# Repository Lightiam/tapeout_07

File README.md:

# Tapeout 07

Controlled repository upload for the Tapeout July_04 work performed so far.

## Start Here

For the manufacturer's current request, use only:

- `00_step01_gerber_bom_only/TFLN_AI_NODE_X2_STEP_01_GERBER_REVIEW.zip`
- `00_step01_gerber_bom_only/TFLN_AI_NODE_X2_STEP_01_BOM.xlsx`

Those are the controlled Step 01 Gerber/BOM review files. The Gerber zip has been refreshed from the post-cleanup KiCad export, and the BOM workbook has been updated to remove stale caution wording, old DRC counts, and old mechanical-reference wording.

## Other Folders

- `01_full_template_outputs`: full template-output package and indexes.
- `02_do_over_vlsi_flow`: VLSI/PCB do-over flow package and response docs.
- `03_schematic_transmittal`: schematic transmittal package and clear dual-NCE/TFLN overview.
- `04_rebuild_eco_required`: reference-envelope rebuild package requiring engineering ECO closure.
- `05_manufacturer_messages`: sendable manufacturer messages and clarification questions.
- `06_engineering_notes`: ECO candidate traceability evidence.
- `07_engineering_reconcile`: latest patched KiCad source and KiCad validation delta.
- `08_fab_release`: fabrication-readiness package — placement audit, fab notes, drill/centroid data, decision log, and release gate.
- `09_pin_complete_data`: pin-data resolution matrix, datasheet manifest, and the engineering data request for the missing NCE/HBM4/TFLN pin maps.
- `10_fab_readiness`: current fab-readiness control point and release-gate verdict. **Start here for fab status.**
- `11_production_fab_roadmap`: real-world sourcing decisions (HBM3E substitute, HyperLight TFLN target) and the locked-layout agent prompt for closing the remaining gaps. **Start here for the active work plan.**
- `99_generation_scripts`: scripts used to generate/assemble these artifacts.

## Engineering Status

Current validated status as of 2026-07-07:

- The repo does not contain a complete design-source schematic or external netlist. The checked KiCad schematic is a connectivity stub: 2,311 lines, 28 wire objects, 82 schematic symbols, and 0 explicit net entries.
- Non-netlist manufacturability cleanup has been applied in `07_engineering_reconcile/00_OPEN_IN_KICAD_PATCHED/`: 4-layer High-Tg FR4 review stackup, ENIG finish metadata, six board-only fiducials, project-local footprint libraries, and silkscreen cleanup.
- The Step 01 BOM workbook now carries current review/signoff language and current validation counts instead of the earlier stale status wording.
- `07_engineering_reconcile/after_non_netlist_fab_readiness_drc.json` reports 0 DRC errors, 0 unconnected items, 82 DRC warnings, and 214 schematic-parity warnings.
- The 82 remaining DRC warnings are all `lib_footprint_mismatch`. The 214 schematic-parity warnings require a real schematic/netlist source and cannot be closed by file cleanup alone.

Post-cleanup Gerber/drill engineering-review export:

- `07_engineering_reconcile/TFLN_AI_NODE_X2_AFTER_NON_NETLIST_CLEANUP_GERBER_DRILL.zip`

## Fabrication Readiness

The `08_fab_release/` package from the remote branch remains in the repo as the fabrication-readiness evidence package: placement audit, fab notes, drill/centroid data, decision log, and release gate. Treat it together with `07_engineering_reconcile/`: production approval still depends on complete schematic/netlist source, parity closure or signed waiver, BOM owner signoff, chassis/mechanical signoff, and manufacturer DFM/DFA closure.

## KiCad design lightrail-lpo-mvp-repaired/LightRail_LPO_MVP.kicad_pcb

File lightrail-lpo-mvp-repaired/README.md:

# LightRail LPO MVP — Manufacturing & Production Package

This package contains the complete manufacturing and SMT assembly deliverables for the **LightRail LPO MVP** board.

## Package Contents

1. **BOM.csv** — Bill of Materials with Designators, Manufacturer Part Numbers (MPNs), Values, Footprints, and Quantities.
2. **CPL.csv** — Component Placement List (Centroid / XY file) containing designator coordinates (X/Y mm, rotation, board layer).
3. **Assembly_Top.svg** — Top-side SMT assembly placement drawing.
4. **Assembly_Bottom.svg** — Bottom-side SMT assembly placement drawing.
5. **KiCad Source Files** — Full PCB design source:
   - `LightRail_LPO_MVP.kicad_pro` (KiCad Project file)
   - `LightRail_LPO_MVP.kicad_sch` (KiCad Schematic file)
   - `LightRail_LPO_MVP.kicad_pcb` (KiCad PCB Layout file)

## Gerber Export Instructions

Gerber plot parameters are pre-configured inside the `LightRail_LPO_MVP.kicad_pcb` source file for automatic plotting. To export:
1. Open `LightRail_LPO_MVP.kicad_pcb` in KiCad Layout Editor.
2. Go to **File → Plot...** (or click the Plot icon).
3. Verify the Output Directory is set to `gerbers/`.
4. Click **Plot** to generate Gerber layers (Copper, Mask, Silk, Paste, Edge.Cuts).
5. Click **Generate Drill Files...** and click **Generate Drill File** to export Excellon drill data.

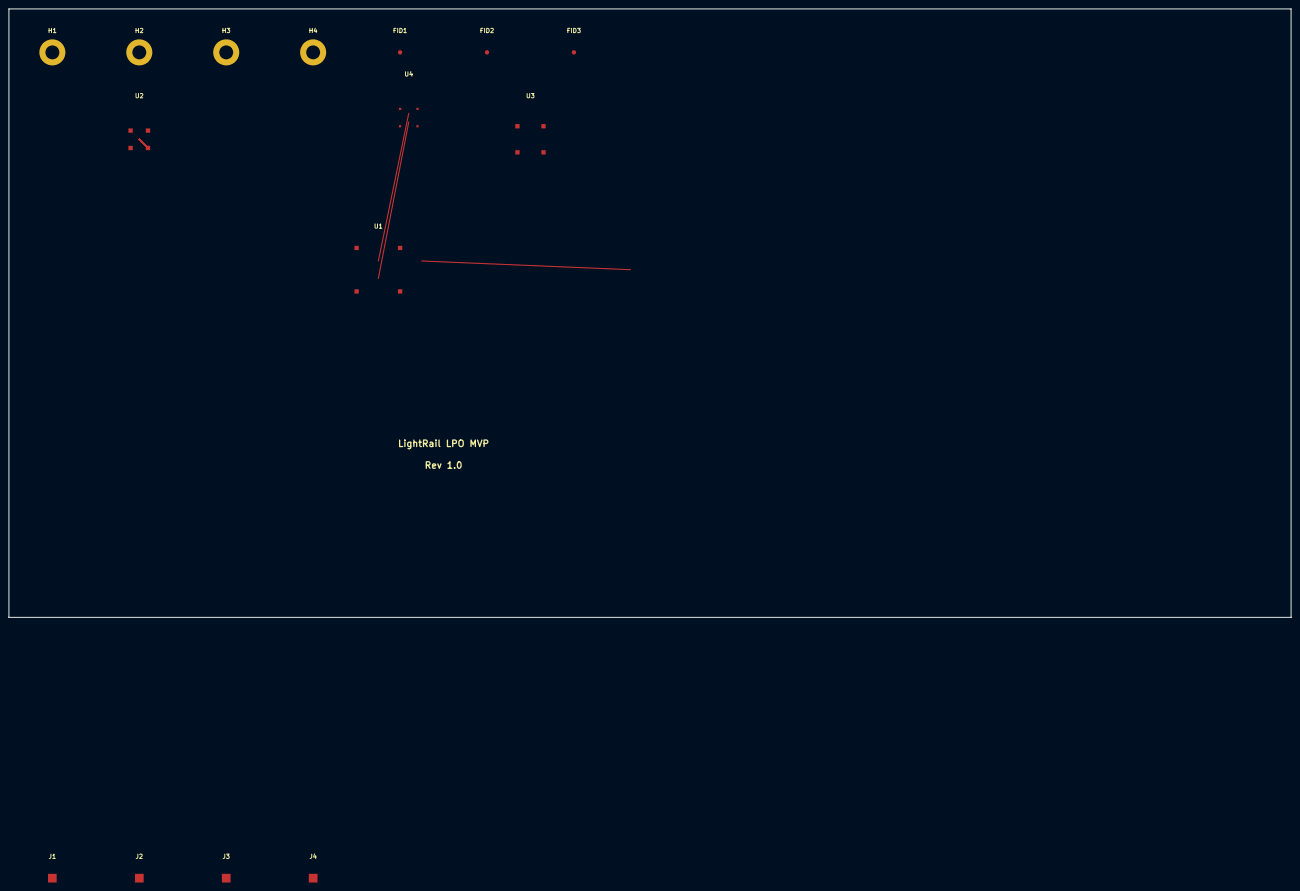
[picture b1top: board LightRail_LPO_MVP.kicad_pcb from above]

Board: 2 copper layers, 295.0 x 140.0 mm, 15 parts (0 on the bottom side), 3 nets.

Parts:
FID1, FID2, FID3: Fiducial; Fiducial_1.0mm_Mask2.0mm
H1, H2, H3, H4: M3; MountingHole_3.2mm_M3
J1, J2, J3, J4: SMA; SMA_Amphenol_132289_EdgeLaunch
U1: TFLN-MZM-400G-C; TFLN_MZM_15mm
U2: TLN-1550-100; DFB_Laser_TO_Can
U3: XPDV4120R; Finisar_XPDV4120R
U4: HMC8410; QFN-24-1EP_4x4mm_P0.5mm_EP2.7x2.7mm

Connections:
net_1: U1.1, U4.1
net_2: U1.2, U4.2
net_3: U1.3, U4.3

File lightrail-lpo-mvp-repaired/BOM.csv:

Designators,Quantity,Manufacturer Part Number,Value,Footprint
"FID1,FID2,FID3",3,"","Fiducial","Fiducial_1.0mm_Mask2.0mm"
"H1,H2,H3,H4",4,"","MountingHole_3.2mm_M3","MountingHole_3.2mm_M3"
"J1,J2,J3,J4",4,"132289","SMA","SMA_Amphenol_132289_EdgeLaunch"
"U1",1,"TFLN-MZM-400G-C","TFLN-MZM-400G-C","TFLN_MZM_15mm"
"U2",1,"TLN-1550-100","TLN-1550-100","DFB_Laser_TO_Can"
"U3",1,"XPDV4120R","XPDV4120R","Finisar_XPDV4120R"
"U4",1,"HMC8410","HMC8410","QFN-24-1EP_4x4mm_P0.5mm_EP2.7x2.7mm"

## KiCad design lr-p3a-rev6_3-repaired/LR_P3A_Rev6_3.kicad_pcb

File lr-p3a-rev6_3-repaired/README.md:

# LR-P3A Rev 6.3 — Manufacturing & Production Package

This package contains the complete manufacturing and SMT assembly deliverables for the **LR-P3A Rev 6.3** board.

## Package Contents

1. **BOM.csv** — Bill of Materials with Designators, Manufacturer Part Numbers (MPNs), Values, Footprints, and Quantities.
2. **CPL.csv** — Component Placement List (Centroid / XY file) containing designator coordinates (X/Y mm, rotation, board layer).
3. **Assembly_Top.svg** — Top-side SMT assembly placement drawing.
4. **Assembly_Bottom.svg** — Bottom-side SMT assembly placement drawing.
5. **KiCad Source Files** — Full PCB design source:
   - `LR_P3A_Rev6_3.kicad_pro` (KiCad Project file)
   - `LR_P3A_Rev6_3.kicad_sch` (KiCad Schematic file)
   - `LR_P3A_Rev6_3.kicad_pcb` (KiCad PCB Layout file)

## Gerber Export Instructions

Gerber plot parameters are pre-configured inside the `LR_P3A_Rev6_3.kicad_pcb` source file for automatic plotting. To export:
1. Open `LR_P3A_Rev6_3.kicad_pcb` in KiCad Layout Editor.
2. Go to **File → Plot...** (or click the Plot icon).
3. Verify the Output Directory is set to `gerbers/`.
4. Click **Plot** to generate Gerber layers (Copper, Mask, Silk, Paste, Edge.Cuts).
5. Click **Generate Drill Files...** and click **Generate Drill File** to export Excellon drill data.

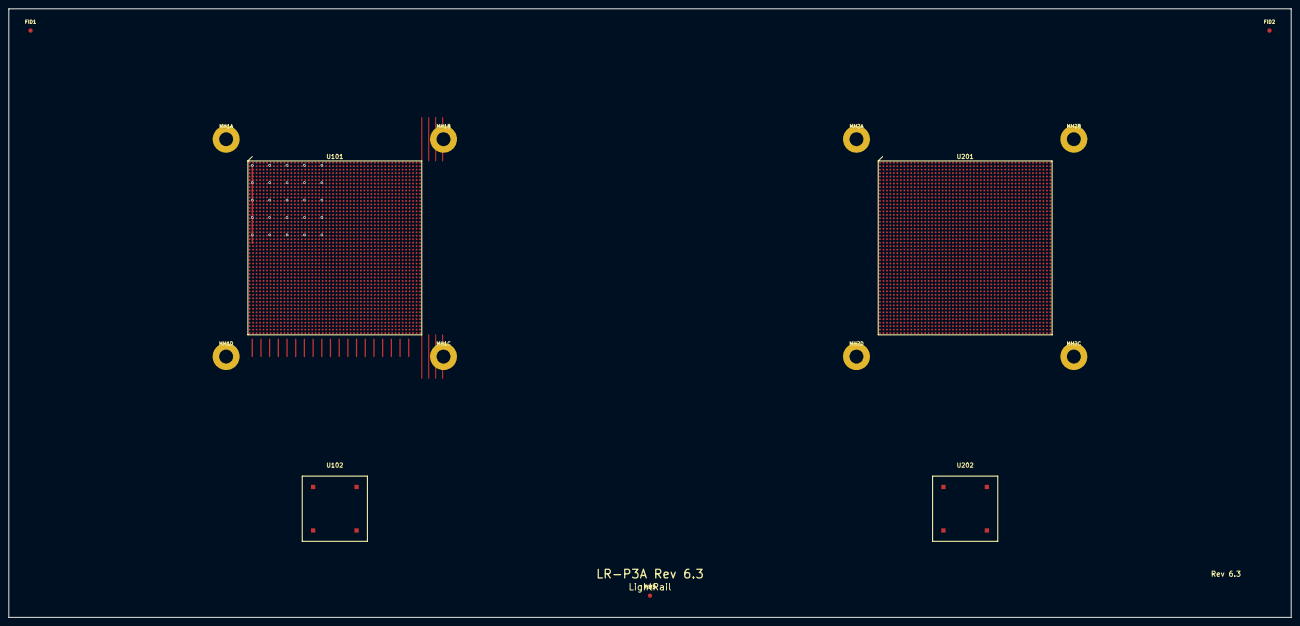
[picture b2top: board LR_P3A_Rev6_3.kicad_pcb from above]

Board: 16 copper layers, 295.0 x 140.0 mm, 15 parts (0 on the bottom side), 10 nets.

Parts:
FID1, FID2, FID3: Fiducial; Fiducial_1mm_Mask2mm
MH1A, MH1B, MH1C, MH1D, MH2A, MH2B, MH2C, MH2D: M3; MountingHole_M3
U101, U201: NCE_BGA_2500; BGA_2500_U101
U102, U202: TFLN_PIC; LGA_U102

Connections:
GND: U101.D26, U101.D27, U101.D28, U101.D29, U101.D30, U101.D31, U101.D32, U101.D33, U101.D34, U101.D35, U101.D36, U101.D37, U101.D38, U101.D39, U101.D40, U101.D41, U101.D42, U101.D43, U101.D44, U101.D45, U101.D46, U101.D47, U101.D48, U101.D49, U101.D50, U101.E1, U101.E2, U101.E3, U101.E4, U101.E5, U101.E6, U101.E7, U101.E8, U101.E9, U101.E10, U101.E11, U101.E12, U101.E13, U101.E14, U101.E15, U101.E16, U101.E17, U101.E18, U101.E19, U101.E20, U101.E21, U101.E22, U101.E23, U101.E24, U101.E25, U101.E26, U101.E27, U101.E28, U101.E29, U101.E30, U101.E31, U101.E32, U101.E33, U101.E34, U101.E35, U101.E36, U101.E37, U101.E38, U101.E39, U101.E40, U101.E41, U101.E42, U101.E43, U101.E44, U101.E45, U101.E46, U101.E47, U101.E48, U101.E49, U101.E50, U101.F1, U101.F2, U101.F3, U101.F4, U101.F5, U101.F6, U101.F7, U101.F8, U101.F9, U101.F10, U101.F11, U101.F12, U101.F13, U101.F14, U101.F15, U101.F16, U101.F17, U101.F18, U101.F19, U101.F20, U101.F21, U101.F22, U101.F23, U101.F24, U101.F25, U101.F26, U101.F27, U101.F28, U101.F29, U101.F30, U101.F31, U101.F32, U101.F33, U101.F34, U101.F35, U101.F36, U101.F37, U101.F38, U101.F39, U101.F40, U101.F41, U101.F42, U101.F43, U101.F44, U101.F45, U101.F46, U101.F47, U101.F48, U101.F49, U101.F50, U102.4, U201.D26, U201.D27, U201.D28, U201.D29, U201.D30, U201.D31, U201.D32, U201.D33, U201.D34, U201.D35, U201.D36, U201.D37, U201.D38, U201.D39, U201.D40, U201.D41, U201.D42, U201.D43, U201.D44, U201.D45, U201.D46, U201.D47, U201.D48, U201.D49, U201.D50, U201.E1, U201.E2, U201.E3, U201.E4, U201.E5, U201.E6, U201.E7, U201.E8, U201.E9, U201.E10, U201.E11, U201.E12, U201.E13, U201.E14, U201.E15, U201.E16, U201.E17, U201.E18, U201.E19, U201.E20, U201.E21, U201.E22, U201.E23, U201.E24, U201.E25, U201.E26, U201.E27, U201.E28, U201.E29, U201.E30, U201.E31, U201.E32, U201.E33, U201.E34, U201.E35, U201.E36, U201.E37, U201.E38, U201.E39, U201.E40, U201.E41, U201.E42, U201.E43, U201.E44, U201.E45, U201.E46, U201.E47, U201.E48, U201.E49, U201.E50, U201.F1, U201.F2, U201.F3, U201.F4, U201.F5, U201.F6, U201.F7, U201.F8, U201.F9, U201.F10, U201.F11, U201.F12, U201.F13, U201.F14, U201.F15, U201.F16, U201.F17, U201.F18, U201.F19, U201.F20, U201.F21, U201.F22, U201.F23, U201.F24, U201.F25, U201.F26, U201.F27, U201.F28, U201.F29, U201.F30, U201.F31, U201.F32, U201.F33, U201.F34, U201.F35, U201.F36, U201.F37, U201.F38, U201.F39, U201.F40, U201.F41, U201.F42, U201.F43, U201.F44, U201.F45, U201.F46, U201.F47, U201.F48, U201.F49, U201.F50, U202.4
HBM4_DQ0: U101.G1, U101.G2, U201.G1, U201.G2
HBM4_DQ1: U101.G3, U101.G4, U201.G3, U201.G4
HBM4_VDDC: U101.A1, U101.A2, U101.A3, U101.A4, U101.A5, U101.A6, U101.A7, U101.A8, U101.A9, U101.A10, U101.A11, U101.A12, U101.A13, U101.A14, U101.A15, U101.A16, U101.A17, U101.A18, U101.A19, U101.A20, U101.A21, U101.A22, U101.A23, U101.A24, U101.A25, U101.A26, U101.A27, U101.A28, U101.A29, U101.A30, U101.A31, U101.A32, U101.A33, U101.A34, U101.A35, U101.A36, U101.A37, U101.A38, U101.A39, U101.A40, U101.A41, U101.A42, U101.A43, U101.A44, U101.A45, U101.A46, U101.A47, U101.A48, U101.A49, U101.A50, U201.A1, U201.A2, U201.A3, U201.A4, U201.A5, U201.A6, U201.A7, U201.A8, U201.A9, U201.A10, U201.A11, U201.A12, U201.A13, U201.A14, U201.A15, U201.A16, U201.A17, U201.A18, U201.A19, U201.A20, U201.A21, U201.A22, U201.A23, U201.A24, U201.A25, U201.A26, U201.A27, U201.A28, U201.A29, U201.A30, U201.A31, U201.A32, U201.A33, U201.A34, U201.A35, U201.A36, U201.A37, U201.A38, U201.A39, U201.A40, U201.A41, U201.A42, U201.A43, U201.A44, U201.A45, U201.A46, U201.A47, U201.A48, U201.A49, U201.A50
HBM4_VDDQ: U101.C1, U101.C2, U101.C3, U101.C4, U101.C5, U101.C6, U101.C7, U101.C8, U101.C9, U101.C10, U101.C11, U101.C12, U101.C13, U101.C14, U101.C15, U101.C16, U101.C17, U101.C18, U101.C19, U101.C20, U101.C21, U101.C22, U101.C23, U101.C24, U101.C25, U101.C26, U101.C27, U101.C28, U101.C29, U101.C30, U101.C31, U101.C32, U101.C33, U101.C34, U101.C35, U101.C36, U101.C37, U101.C38, U101.C39, U101.C40, U101.C41, U101.C42, U101.C43, U101.C44, U101.C45, U101.C46, U101.C47, U101.C48, U101.C49, U101.C50, U201.C1, U201.C2, U201.C3, U201.C4, U201.C5, U201.C6, U201.C7, U201.C8, U201.C9, U201.C10, U201.C11, U201.C12, U201.C13, U201.C14, U201.C15, U201.C16, U201.C17, U201.C18, U201.C19, U201.C20, U201.C21, U201.C22, U201.C23, U201.C24, U201.C25, U201.C26, U201.C27, U201.C28, U201.C29, U201.C30, U201.C31, U201.C32, U201.C33, U201.C34, U201.C35, U201.C36, U201.C37, U201.C38, U201.C39, U201.C40, U201.C41, U201.C42, U201.C43, U201.C44, U201.C45, U201.C46, U201.C47, U201.C48, U201.C49, U201.C50
HBM4_VDDQL: U101.B1, U101.B2, U101.B3, U101.B4, U101.B5, U101.B6, U101.B7, U101.B8, U101.B9, U101.B10, U101.B11, U101.B12, U101.B13, U101.B14, U101.B15, U101.B16, U101.B17, U101.B18, U101.B19, U101.B20, U101.B21, U101.B22, U101.B23, U101.B24, U101.B25, U101.B26, U101.B27, U101.B28, U101.B29, U101.B30, U101.B31, U101.B32, U101.B33, U101.B34, U101.B35, U101.B36, U101.B37, U101.B38, U101.B39, U101.B40, U101.B41, U101.B42, U101.B43, U101.B44, U101.B45, U101.B46, U101.B47, U101.B48, U101.B49, U101.B50, U201.B1, U201.B2, U201.B3, U201.B4, U201.B5, U201.B6, U201.B7, U201.B8, U201.B9, U201.B10, U201.B11, U201.B12, U201.B13, U201.B14, U201.B15, U201.B16, U201.B17, U201.B18, U201.B19, U201.B20, U201.B21, U201.B22, U201.B23, U201.B24, U201.B25, U201.B26, U201.B27, U201.B28, U201.B29, U201.B30, U201.B31, U201.B32, U201.B33, U201.B34, U201.B35, U201.B36, U201.B37, U201.B38, U201.B39, U201.B40, U201.B41, U201.B42, U201.B43, U201.B44, U201.B45, U201.B46, U201.B47, U201.B48, U201.B49, U201.B50
HBM4_VPP: U101.D1, U101.D2, U101.D3, U101.D4, U101.D5, U101.D6, U101.D7, U101.D8, U101.D9, U101.D10, U101.D11, U101.D12, U101.D13, U101.D14, U101.D15, U101.D16, U101.D17, U101.D18, U101.D19, U101.D20, U101.D21, U101.D22, U101.D23, U101.D24, U101.D25, U201.D1, U201.D2, U201.D3, U201.D4, U201.D5, U201.D6, U201.D7, U201.D8, U201.D9, U201.D10, U201.D11, U201.D12, U201.D13, U201.D14, U201.D15, U201.D16, U201.D17, U201.D18, U201.D19, U201.D20, U201.D21, U201.D22, U201.D23, U201.D24, U201.D25
OPTICAL_RX: U102.2, U202.2
OPTICAL_TX: U102.1, U202.1
VCC_3V3: U102.3, U202.3

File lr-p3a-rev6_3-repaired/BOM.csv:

Designators,Quantity,Manufacturer Part Number,Value,Footprint
"U101,U201",2,"NCE-2500-BGA-40","NCE_BGA_2500","BGA_2500_U101"
"U102,U202",2,"TFLN-PIC-MOD-01","TFLN_PIC","LGA_U102"

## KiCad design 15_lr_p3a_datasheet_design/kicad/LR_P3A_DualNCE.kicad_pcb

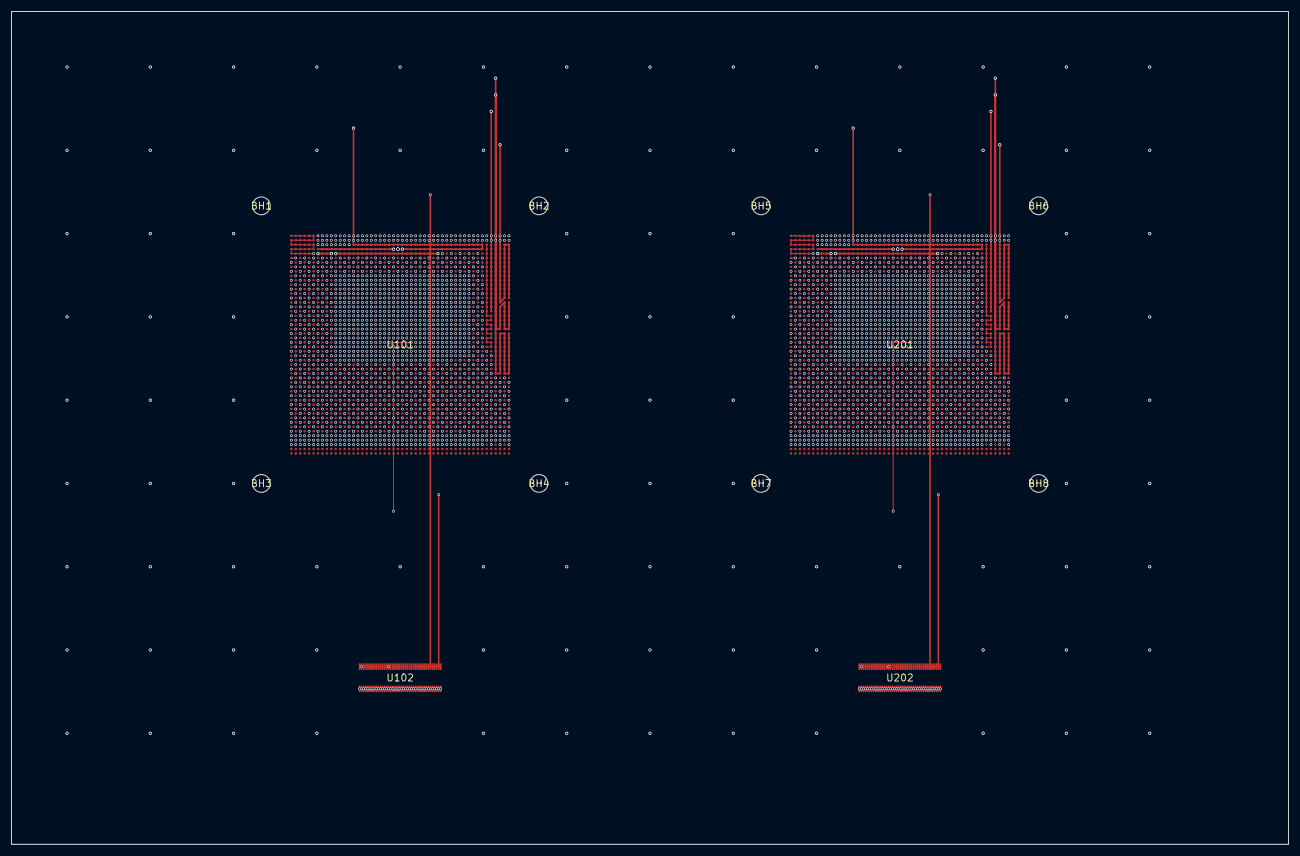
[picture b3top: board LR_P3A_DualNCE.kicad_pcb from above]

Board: 16 copper layers, 230.0 x 150.0 mm, 12 parts (0 on the bottom side), 26 nets.

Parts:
BH1, BH2, BH3, BH4, BH5, BH6, BH7, BH8: (no value)
U101, U201: BGA-2500_40x40_P0.8mm_NCE
U102, U202: TFLN-MZM-400G-C

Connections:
+0V9: U102.35, U102.36, U102.37, U102.38, U202.35, U202.36, U202.37, U202.38
+3V3: U102.39, U102.40, U202.39, U202.40
BIAS_TUNE_A: U102.17, U102.18, U102.19, U102.20, U102.21, U102.22, U102.23, U102.24
BIAS_TUNE_B: U202.17, U202.18, U202.19, U202.20, U202.21, U202.22, U202.23, U202.24
GND: U101.AA1, U101.AA3, U101.AA5, U101.AA7, U101.AA9, U101.AA43, U101.AB2, U101.AB4, U101.AB6, U101.AB8, U101.AB10, U101.AB42, U101.AB44, U101.AC1, U101.AC3, U101.AC5, U101.AC7, U101.AC9, U101.AC43, U101.AD2, U101.AD4, U101.AD6, U101.AD8, U101.AD10, U101.AD42, U101.AD44, U101.AE1, U101.AE3, U101.AE5, U101.AE7, U101.AE9, U101.AE43, U101.AF2, U101.AF4, U101.AF6, U101.AF8, U101.AF10, U101.AF42, U101.AF44, U101.AG1, U101.AG3, U101.AG5, U101.AG7, U101.AG9, U101.AG43, U101.AG45, U101.AH2, U101.AH4, U101.AH6, U101.AH8, U101.AH10, U101.AH42, U101.AH44, U101.AH46, U101.AJ1, U101.AJ3, U101.AJ5, U101.AJ7, U101.AJ9, U101.AJ39, U101.AJ41, U101.AJ43, U101.AJ45, U101.AK2, U101.AK4, U101.AK6, U101.AK8, U101.AK10, U101.AK12, U101.AK14, U101.AK16, U101.AK18, U101.AK20, U101.AK22, U101.AK24, U101.AK26, U101.AK28, U101.AK30, U101.AK32, U101.AK34, U101.AK36, U101.AK38, U101.AK40, U101.AK42, U101.AK44, U101.AK46, U101.AL1, U101.AL3, U101.AL5, U101.AL7, U101.AL9, U101.AL11, U101.AL13, U101.AL15, U101.AL17, U101.AL19, U101.AL21, U101.AL23, U101.AL25, U101.AL27, U101.AL29, U101.AL31, U101.AL33, U101.AL35, U101.AL37, U101.AL39, U101.AL41, U101.AL43, U101.AL45, U101.AM2, U101.AM4, U101.AM6, U101.AM8, U101.AM10, U101.AM12, U101.AM14, U101.AM16, U101.AM18, U101.AM20, U101.AM22, U101.AM24, U101.AM26, U101.AM28, U101.AM30, U101.AM32, U101.AM34, U101.AM36, U101.AM38, U101.AM40, U101.AM42, U101.AM44, U101.AM46, U101.AN1, U101.AN3, U101.AN5, U101.AN7, U101.AN9, U101.AN11, U101.AN13, U101.AN15, U101.AN17, U101.AN19, U101.AN21, U101.AN23, U101.AN25, U101.AN27, U101.AN29, U101.AN31, U101.AN33, U101.AN35, U101.AN37, U101.AN39, U101.AN41, U101.AN43, U101.AN45, U101.AN47, U101.AN49, U101.AP2, U101.AP4, U101.AP6, U101.AP8, U101.AP10, U101.AP12, U101.AP14, U101.AP16, U101.AP18, U101.AP20, U101.AP22, U101.AP24, U101.AP26, U101.AP28, U101.AP30, U101.AP32, U101.AP34, U101.AP36, U101.AP38, U101.AP40, U101.AP42, U101.AP44, U101.AP46, U101.AP48, U101.AP50, U101.AR1, U101.AR3, U101.AR5, U101.AR7, U101.AR9, U101.AR11, U101.AR13, U101.AR15, U101.AR17, U101.AR19, U101.AR21, U101.AR23, U101.AR25, U101.AR27, U101.AR29, U101.AR31, U101.AR33, U101.AR35, U101.AR37, U101.AR39, U101.AR41, U101.AR43, U101.AR45, U101.AR47, U101.AR49, U101.AT2, U101.AT4, U101.AT6, U101.AT8, U101.AT10, U101.AT12, U101.AT14, U101.AT16, U101.AT18, U101.AT20, U101.AT22, U101.AT24, U101.AT26, U101.AT28, U101.AT30, U101.AT32, U101.AT34, U101.AT36, U101.AT38, U101.AT40, U101.AT42, U101.AT44, U101.AT46, U101.AT48, U101.AT50, U101.AU1, U101.AU3, U101.AU5, U101.AU7, U101.AU9, U101.AU11, U101.AU13, U101.AU15, U101.AU17, U101.AU19, U101.AU21, U101.AU23, U101.AU25, U101.AU27, U101.AU29, U101.AU31, U101.AU33, U101.AU35, U101.AU37, U101.AU39, U101.AU41, U101.AU43, U101.AU45, U101.AU47, U101.AU49, U101.AV2, U101.AV4, U101.AV6, U101.AV8, U101.AV10, U101.AV12, U101.AV14, U101.AV16, U101.AV18, U101.AV20, U101.AV22, U101.AV24, U101.AV26, U101.AV28, U101.AV30, U101.AV32, U101.AV34, U101.AV36, U101.AV38, U101.AV40, U101.AV42, U101.AV44, U101.AV46, U101.AV48, U101.AV50, U101.AW1, U101.AW3, U101.AW5, U101.AW7, U101.AW9, U101.AW11, U101.AW13, U101.AW15, U101.AW17, U101.AW19, U101.AW21, U101.AW23, U101.AW25, U101.AW27, U101.AW29, U101.AW31, U101.AW33, U101.AW35, U101.AW37, U101.AW39, U101.AW41, U101.AW43, U101.AW45, U101.AW47, U101.AW49, U101.AY2, U101.AY4, U101.AY6, U101.AY8, U101.AY10, U101.AY12, U101.AY14, U101.AY16, U101.AY18, U101.AY20, U101.AY22, U101.AY24, U101.AY26, U101.AY28, U101.AY30, U101.AY32, U101.AY34, U101.AY36, U101.AY38, U101.AY40, U101.AY42, U101.AY44, U101.AY46, U101.AY48, U101.AY50, U101.BA1, U101.BA3, U101.BA5, U101.BA7, U101.BA9, U101.BA11, U101.BA13, U101.BA15, U101.BA17, U101.BA19, U101.BA21, U101.BA23, U101.BA25, U101.BA27, U101.BA29, U101.BA31, U101.BA33, U101.BA35, U101.BA37, U101.BA39, U101.BA41, U101.BA43, U101.BA45, U101.BA47, U101.BA49, U101.BB2, U101.BB4, U101.BB6, U101.BB8, U101.BB10, U101.BB12, U101.BB14, U101.BB16, U101.BB18, U101.BB20, U101.BB22, U101.BB24, U101.BB26, U101.BB28, U101.BB30, U101.BB32, U101.BB34, U101.BB36, U101.BB38, U101.BB40, U101.BB42, U101.BB44, U101.BB46, U101.BB48, U101.BB50, U101.BC1, U101.BC3, U101.BC5, U101.BC7, U101.BC9, U101.BC11, U101.BC13, U101.BC15, U101.BC17, U101.BC19, U101.BC21, U101.BC23, U101.BC25, U101.BC27, U101.BC29, U101.BC31, U101.BC33, U101.BC35, U101.BC37, U101.BC39, U101.BC41, U101.BC43, U101.BC45, U101.BC47, U101.BC49, U101.BD2, U101.BD4, U101.BD6, U101.BD8, U101.BD10, U101.BD12, U101.BD14, U101.BD16, U101.BD18, U101.BD20, U101.BD22, U101.BD24, U101.BD26, U101.BD28, U101.BD30, U101.BD32, U101.BD34, U101.BD36, U101.BD38, U101.BD40, U101.BD42, U101.BD44, U101.BD46, U101.BD48, U101.BD50, U101.BE1, U101.BE3, U101.BE5, U101.BE7, U101.BE9, U101.BE11, U101.BE13, U101.BE15, U101.BE17, U101.BE19, U101.BE21, U101.BE23, U101.BE25, U101.BE27, U101.BE29, U101.BE31, U101.BE33, U101.BE35, U101.BE37, U101.BE39, U101.BE41, U101.BE43, U101.BE45, U101.BE47, U101.BE49, U101.BH46, U101.BH48, U101.BH50, U101.E35, U101.E37, U101.E39, U101.E41, U101.E43, U101.F4, U101.F6, U101.F8, U101.F10, U101.F12, U101.F14, U101.F16, U101.F18, U101.F20, U101.F22, U101.F24, U101.F26, U101.F28, U101.F30, U101.F32, U101.F34, U101.F36, U101.F38, U101.F40, U101.F42, U101.F44, U101.G1, U101.G3, U101.G5, U101.G7, U101.G9, U101.G11, U101.G13, U101.G15, U101.G17, U101.G19, U101.G21, U101.G23, U101.G25, U101.G27, U101.G29, U101.G31, U101.G33, U101.G35, U101.G37, U101.G39, U101.G41, U101.G43, U101.H2, U101.H4, U101.H6, U101.H8, U101.H10, U101.H12, U101.H14, U101.H16, U101.H18, U101.H20, U101.H22, U101.H24, U101.H26, U101.H28, U101.H30, U101.H32, U101.H34, U101.H36, U101.H38, U101.H40, U101.H42, U101.H44, U101.J1, U101.J3, U101.J5, U101.J7, U101.J9, U101.J11, U101.J13, U101.J15, U101.J17, U101.J19, U101.J21, U101.J23, U101.J25, U101.J27, U101.J29, U101.J31, U101.J33, U101.J35, U101.J37, U101.J39, U101.J41, U101.J43, U101.K2, U101.K4, U101.K6, U101.K8, U101.K10, U101.K42, U101.K44, U101.L1, U101.L3, U101.L5, U101.L7, U101.L9, U101.L43, U101.M2, U101.M4, U101.M6, U101.M8, U101.M10, U101.M42, U101.M44, U101.N1, U101.N3, U101.N5, U101.N7, U101.N9, U101.N43, U101.P2, U101.P4, U101.P6, U101.P8, U101.P10, U101.P42, U101.P44, U101.R1, U101.R3, U101.R5, U101.R7, U101.R9, U101.R43, U101.T2, U101.T4, U101.T6, U101.T8, U101.T10, U101.T42, U101.T44, U101.U1, U101.U3, U101.U5, U101.U7, U101.U9, U101.U43, U101.V2, U101.V4, U101.V6, U101.V8, U101.V10, U101.V42, U101.V44, U101.W1, U101.W3, U101.W5, U101.W7, U101.W9, U101.W43, U101.Y2, U101.Y4, U101.Y6, U101.Y8, U101.Y10, U101.Y42, U101.Y44, U102.41, U102.42, U102.43, U102.44, U102.45, U102.46, U102.47, U102.48, U102.49, U102.50, U102.51, U102.52, U102.53, U102.54, U102.55, U102.56, U102.57, U102.58, U102.59, U102.60, U102.61, U102.62, U102.63, U102.64, U102.65, U102.66, U102.67, U102.68, U102.69, U102.70, U102.71, U102.72, U102.73, U102.74, U102.75, U102.76, U102.77, U102.78, U102.79, U102.80, U201.AA1, U201.AA3, U201.AA5, U201.AA7, U201.AA9, U201.AA43, U201.AB2, U201.AB4, U201.AB6, U201.AB8, U201.AB10, U201.AB42, U201.AB44, U201.AC1, U201.AC3, U201.AC5, U201.AC7, U201.AC9, U201.AC43, U201.AD2, U201.AD4, U201.AD6, U201.AD8, U201.AD10, U201.AD42, U201.AD44, U201.AE1, U201.AE3, U201.AE5, U201.AE7, U201.AE9, U201.AE43, U201.AF2, U201.AF4, U201.AF6, U201.AF8, U201.AF10, U201.AF42, U201.AF44, U201.AG1, U201.AG3, U201.AG5, U201.AG7, U201.AG9, U201.AG43, U201.AG45, U201.AH2, U201.AH4, U201.AH6, U201.AH8, U201.AH10, U201.AH42, U201.AH44, U201.AH46, U201.AJ1, U201.AJ3, U201.AJ5, U201.AJ7, U201.AJ9, U201.AJ39, U201.AJ41, U201.AJ43, U201.AJ45, U201.AK2, U201.AK4, U201.AK6, U201.AK8, U201.AK10, U201.AK12, U201.AK14, U201.AK16, U201.AK18, U201.AK20, U201.AK22, U201.AK24, U201.AK26, U201.AK28, U201.AK30, U201.AK32, U201.AK34, U201.AK36, U201.AK38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
HBM4_SIDECH_A: U101.AA45, U101.AA46, U101.AB45, U101.AB46, U101.AC45, U101.AC46, U101.AD45, U101.AD46, U101.AE45, U101.AE46, U101.AF45, U101.AF46, U101.C45, U101.D45, U101.E45, U101.F45, U101.G45, U101.H45, U101.J45, U101.K45, U101.L45, U101.M45, U101.N45, U101.P45, U101.R45, U101.T45, U101.U45, U101.V45, U101.W45, U101.W46, U101.Y45, U101.Y46
HBM4_SIDECH_B: U201.AA45, U201.AA46, U201.AB45, U201.AB46, U201.AC45, U201.AC46, U201.AD45, U201.AD46, U201.AE45, U201.AE46, U201.AF45, U201.AF46, U201.C45, U201.D45, U201.E45, U201.F45, U201.G45, U201.H45, U201.J45, U201.K45, U201.L45, U201.M45, U201.N45, U201.P45, U201.R45, U201.T45, U201.U45, U201.V45, U201.W45, U201.W46, U201.Y45, U201.Y46
HBM4_VDDC: U101.C48, U101.C49, U101.C50, U101.D48, U101.D49, U101.D50, U101.E48, U101.E49, U101.E50, U101.F48, U101.F49, U101.F50, U101.G48, U101.G49, U101.G50, U101.H48, U101.H49, U101.H50, U101.J48, U101.J49, U101.J50, U101.K48, U101.K49, U101.K50, U101.L48, U101.L49, U101.L50, U101.M48, U101.M49, U101.M50, U101.N48, U101.N49, U101.N50, U101.P48, U101.P49, U101.P50, U101.R48, U101.R49, U101.R50, U101.T48, U201.C48, U201.C49, U201.C50, U201.D48, U201.D49, U201.D50, U201.E48, U201.E49, U201.E50, U201.F48, U201.F49, U201.F50, U201.G48, U201.G49, U201.G50, U201.H48, U201.H49, U201.H50, U201.J48, U201.J49, U201.J50, U201.K48, U201.K49, U201.K50, U201.L48, U201.L49, U201.L50, U201.M48, U201.M49, U201.M50, U201.N48, U201.N49, U201.N50, U201.P48, U201.P49, U201.P50, U201.R48, U201.R49, U201.R50, U201.T48
HBM4_VDDQ: U101.AC47, U101.AC48, U101.AC49, U101.AC50, U101.AD47, U101.AD48, U101.AD49, U101.AD50, U101.AE47, U101.AE48, U101.AE49, U101.AE50, U101.AF47, U101.AF48, U101.AF49, U101.AF50, U101.AG47, U101.AG48, U101.AG49, U101.AG50, U101.AH47, U101.AH48, U101.AH49, U101.AH50, U101.AJ47, U101.AJ48, U101.AJ49, U101.AJ50, U101.AK47, U101.AK48, U101.AK49, U101.AK50, U101.AL47, U101.AL48, U101.AL49, U101.AL50, U101.AM47, U101.AM48, U101.AM49, U101.AM50, U201.AC47, U201.AC48, U201.AC49, U201.AC50, U201.AD47, U201.AD48, U201.AD49, U201.AD50, U201.AE47, U201.AE48, U201.AE49, U201.AE50, U201.AF47, U201.AF48, U201.AF49, U201.AF50, U201.AG47, U201.AG48, U201.AG49, U201.AG50, U201.AH47, U201.AH48, U201.AH49, U201.AH50, U201.AJ47, U201.AJ48, U201.AJ49, U201.AJ50, U201.AK47, U201.AK48, U201.AK49, U201.AK50, U201.AL47, U201.AL48, U201.AL49, U201.AL50, U201.AM47, U201.AM48, U201.AM49, U201.AM50
HBM4_VDDQL: U101.AA47, U101.AA48, U101.AA49, U101.AA50, U101.AB47, U101.AB48, U101.AB49, U101.AB50, U101.C47, U101.D47, U101.E47, U101.F47, U101.G47, U101.H47, U101.J47, U101.K47, U101.L47, U101.M47, U101.N47, U101.P47, U101.R47, U101.T47, U101.T49, U101.T50, U101.U47, U101.U48, U101.U49, U101.U50, U101.V47, U101.V48, U101.V49, U101.V50, U101.W47, U101.W48, U101.W49, U101.W50, U101.Y47, U101.Y48, U101.Y49, U101.Y50, U201.AA47, U201.AA48, U201.AA49, U201.AA50, U201.AB47, U201.AB48, U201.AB49, U201.AB50, U201.C47, U201.D47, U201.E47, U201.F47, U201.G47, U201.H47, U201.J47, U201.K47, U201.L47, U201.M47, U201.N47, U201.P47, U201.R47, U201.T47, U201.T49, U201.T50, U201.U47, U201.U48, U201.U49, U201.U50, U201.V47, U201.V48, U201.V49, U201.V50, U201.W47, U201.W48, U201.W49, U201.W50, U201.Y47, U201.Y48, U201.Y49, U201.Y50
HBM4_VPP: U101.C46, U101.D46, U101.E46, U101.F46, U101.G46, U101.H46, U101.J46, U101.K46, U101.L46, U101.M46, U101.N46, U101.P46, U101.R46, U101.T46, U101.U46, U101.V46, U201.C46, U201.D46, U201.E46, U201.F46, U201.G46, U201.H46, U201.J46, U201.K46, U201.L46, U201.M46, U201.N46, U201.P46, U201.R46, U201.T46, U201.U46, U201.V46
MGMT_A: U101.A1, U101.A2, U101.A3, U101.A4, U101.A5, U101.A6, U101.B1, U101.B2, U101.B3, U101.B4, U101.B5, U101.B6, U101.C1, U101.C2, U101.C3, U101.C4, U101.C5, U101.C6, U101.D1, U101.D2, U101.D3, U101.D4, U101.D5, U101.D6, U101.E1, U101.E2, U101.E3, U101.E4, U101.E5, U101.E6, U101.F1, U101.F2
MGMT_B: U201.A1, U201.A2, U201.A3, U201.A4, U201.A5, U201.A6, U201.B1, U201.B2, U201.B3, U201.B4, U201.B5, U201.B6, U201.C1, U201.C2, U201.C3, U201.C4, U201.C5, U201.C6, U201.D1, U201.D2, U201.D3, U201.D4, U201.D5, U201.D6, U201.E1, U201.E2, U201.E3, U201.E4, U201.E5, U201.E6, U201.F1, U201.F2
PCIE_G6_A: U101.BF1, U101.BF2, U101.BF3, U101.BF4, U101.BF5, U101.BF6, U101.BF7, U101.BF8, U101.BF9, U101.BF10, U101.BF11, U101.BF12, U101.BF13, U101.BF14, U101.BF15, U101.BF16, U101.BF17, U101.BF18, U101.BF19, U101.BF20, U101.BF21, U101.BF22, U101.BF23, U101.BF24, U101.BF25, U101.BF26, U101.BF27, U101.BF28, U101.BF29, U101.BF30, U101.BF31, U101.BF32, U101.BF33, U101.BF34, U101.BF35, U101.BF36, U101.BF37, U101.BF38, U101.BF39, U101.BF40, U101.BF41, U101.BF42, U101.BF43, U101.BF44, U101.BF45, U101.BF46, U101.BF47, U101.BF48, U101.BF49, U101.BF50, U101.BG1, U101.BG2, U101.BG3, U101.BG4, U101.BG5, U101.BG6, U101.BG7, U101.BG8, U101.BG9, U101.BG10, U101.BG11, U101.BG12, U101.BG13, U101.BG14, U101.BG15, U101.BG16, U101.BG17, U101.BG18, U101.BG19, U101.BG20, U101.BG21, U101.BG22, U101.BG23, U101.BG24, U101.BG25, U101.BG26, U101.BG27, U101.BG28, U101.BG29, U101.BG30, U101.BG31, U101.BG32, U101.BG33, U101.BG34, U101.BG35, U101.BG36, U101.BG37, U101.BG38, U101.BG39, U101.BG40, U101.BG41, U101.BG42, U101.BG43, U101.BG44, U101.BG45, U101.BG46, U101.BG47, U101.BG48, U101.BG49, U101.BG50, U101.BH1, U101.BH2, U101.BH3, U101.BH4, U101.BH5, U101.BH6, U101.BH7, U101.BH8, U101.BH9, U101.BH10, U101.BH11, U101.BH12, U101.BH13, U101.BH14, U101.BH15, U101.BH16, U101.BH17, U101.BH18, U101.BH19, U101.BH20, U101.BH21, U101.BH22, U101.BH23, U101.BH24, U101.BH25, U101.BH26, U101.BH27, U101.BH28, U101.BH29, U101.BH30, U101.BH31, U101.BH32, U101.BH33, U101.BH34, U101.BH35, U101.BH36, U101.BH37, U101.BH38, U101.BH39, U101.BH40, U101.BH41, U101.BH42, U101.BH43, U101.BH44
PCIE_G6_B: U201.BF1, U201.BF2, U201.BF3, U201.BF4, U201.BF5, U201.BF6, U201.BF7, U201.BF8, U201.BF9, U201.BF10, U201.BF11, U201.BF12, U201.BF13, U201.BF14, U201.BF15, U201.BF16, U201.BF17, U201.BF18, U201.BF19, U201.BF20, U201.BF21, U201.BF22, U201.BF23, U201.BF24, U201.BF25, U201.BF26, U201.BF27, U201.BF28, U201.BF29, U201.BF30, U201.BF31, U201.BF32, U201.BF33, U201.BF34, U201.BF35, U201.BF36, U201.BF37, U201.BF38, U201.BF39, U201.BF40, U201.BF41, U201.BF42, U201.BF43, U201.BF44, U201.BF45, U201.BF46, U201.BF47, U201.BF48, U201.BF49, U201.BF50, U201.BG1, U201.BG2, U201.BG3, U201.BG4, U201.BG5, U201.BG6, U201.BG7, U201.BG8, U201.BG9, U201.BG10, U201.BG11, U201.BG12, U201.BG13, U201.BG14, U201.BG15, U201.BG16, U201.BG17, U201.BG18, U201.BG19, U201.BG20, U201.BG21, U201.BG22, U201.BG23, U201.BG24, U201.BG25, U201.BG26, U201.BG27, U201.BG28, U201.BG29, U201.BG30, U201.BG31, U201.BG32, U201.BG33, U201.BG34, U201.BG35, U201.BG36, U201.BG37, U201.BG38, U201.BG39, U201.BG40, U201.BG41, U201.BG42, U201.BG43, U201.BG44, U201.BG45, U201.BG46, U201.BG47, U201.BG48, U201.BG49, U201.BG50, U201.BH1, U201.BH2, U201.BH3, U201.BH4, U201.BH5, U201.BH6, U201.BH7, U201.BH8, U201.BH9, U201.BH10, U201.BH11, U201.BH12, U201.BH13, U201.BH14, U201.BH15, U201.BH16, U201.BH17, U201.BH18, U201.BH19, U201.BH20, U201.BH21, U201.BH22, U201.BH23, U201.BH24, U201.BH25, U201.BH26, U201.BH27, U201.BH28, U201.BH29, U201.BH30, U201.BH31, U201.BH32, U201.BH33, U201.BH34, U201.BH35, U201.BH36, U201.BH37, U201.BH38, U201.BH39, U201.BH40, U201.BH41, U201.BH42, U201.BH43, U201.BH44
PD_MON_A: U102.27, U102.28, U102.29, U102.30, U102.31, U102.32, U102.33, U102.34
PD_MON_B: U202.27, U202.28, U202.29, U202.30, U202.31, U202.32, U202.33, U202.34
PWR_CORE: U101.AA11, U101.AA12, U101.AA13, U101.AA14, U101.AA15, U101.AA16, U101.AA17, U101.AA18, U101.AA19, U101.AA20, U101.AA21, U101.AA22, U101.AA23, U101.AA24, U101.AA25, U101.AA26, U101.AA27, U101.AA28, U101.AA29, U101.AA30, U101.AA31, U101.AA32, U101.AA33, U101.AA34, U101.AA35, U101.AA36, U101.AA37, U101.AA38, U101.AA39, U101.AA40, U101.AA41, U101.AB11, U101.AB12, U101.AB13, U101.AB14, U101.AB15, U101.AB16, U101.AB17, U101.AB18, U101.AB19, U101.AB20, U101.AB21, U101.AB22, U101.AB23, U101.AB24, U101.AB25, U101.AB26, U101.AB27, U101.AB28, U101.AB29, U101.AB30, U101.AB31, U101.AB32, U101.AB33, U101.AB34, U101.AB35, U101.AB36, U101.AB37, U101.AB38, U101.AB39, U101.AB40, U101.AB41, U101.AC11, U101.AC12, U101.AC13, U101.AC14, U101.AC15, U101.AC16, U101.AC17, U101.AC18, U101.AC19, U101.AC20, U101.AC21, U101.AC22, U101.AC23, U101.AC24, U101.AC25, U101.AC26, U101.AC27, U101.AC28, U101.AC29, U101.AC30, U101.AC31, U101.AC32, U101.AC33, U101.AC34, U101.AC35, U101.AC36, U101.AC37, U101.AC38, U101.AC39, U101.AC40, U101.AC41, U101.AD11, U101.AD12, U101.AD13, U101.AD14, U101.AD15, U101.AD16, U101.AD17, U101.AD18, U101.AD19, U101.AD20, U101.AD21, U101.AD22, U101.AD23, U101.AD24, U101.AD25, U101.AD26, U101.AD27, U101.AD28, U101.AD29, U101.AD30, U101.AD31, U101.AD32, U101.AD33, U101.AD34, U101.AD35, U101.AD36, U101.AD37, U101.AD38, U101.AD39, U101.AD40, U101.AD41, U101.AE11, U101.AE12, U101.AE13, U101.AE14, U101.AE15, U101.AE16, U101.AE17, U101.AE18, U101.AE19, U101.AE20, U101.AE21, U101.AE22, U101.AE23, U101.AE28, U101.AE29, U101.AE30, U101.AE31, U101.AE32, U101.AE33, U101.AE34, U101.AE35, U101.AE36, U101.AE37, U101.AE38, U101.AE39, U101.AE40, U101.AE41, U101.AF11, U101.AF12, U101.AF13, U101.AF14, U101.AF15, U101.AF16, U101.AF17, U101.AF18, U101.AF19, U101.AF20, U101.AF21, U101.AF22, U101.AF23, U101.AF24, U101.AF25, U101.AF26, U101.AF27, U101.AF28, U101.AF29, U101.AF30, U101.AF31, U101.AF32, U101.AF33, U101.AF34, U101.AF35, U101.AF36, U101.AF37, U101.AF38, U101.AF39, U101.AF40, U101.AF41, U101.AG11, U101.AG12, U101.AG13, U101.AG14, U101.AG15, U101.AG16, U101.AG17, U101.AG18, U101.AG19, U101.AG20, U101.AG21, U101.AG22, U101.AG23, U101.AG24, U101.AG25, U101.AG26, U101.AG27, U101.AG28, U101.AG29, U101.AG30, U101.AG31, U101.AG32, U101.AG33, U101.AG34, U101.AG35, U101.AG36, U101.AG37, U101.AG38, U101.AG39, U101.AG40, U101.AG41, U101.AH11, U101.AH12, U101.AH13, U101.AH14, U101.AH15, U101.AH16, U101.AH17, U101.AH18, U101.AH19, U101.AH20, U101.AH21, U101.AH22, U101.AH23, U101.AH24, U101.AH25, U101.AH26, U101.AH27, U101.AH28, U101.AH29, U101.AH30, U101.AH31, U101.AH32, U101.AH33, U101.AH34, U101.AH35, U101.AH36, U101.AH37, U101.AH38, U101.AH39, U101.AH40, U101.AH41, U101.AJ11, U101.AJ12, U101.AJ13, U101.AJ14, U101.AJ15, U101.AJ16, U101.AJ17, U101.AJ18, U101.AJ19, U101.AJ20, U101.AJ21, U101.AJ22, U101.AJ23, U101.AJ24, U101.AJ25, U101.AJ26, U101.AJ27, U101.AJ28, U101.AJ29, U101.AJ30, U101.AJ31, U101.AJ32, U101.AJ33, U101.AJ34, U101.AJ35, U101.AJ36, U101.AJ37, U101.K11, U101.K12, U101.K13, U101.K14, U101.K15, U101.K16, U101.K17, U101.K18, U101.K19, U101.K20, U101.K21, U101.K22, U101.K23, U101.K24, U101.K25, U101.K26, U101.K27, U101.K28, U101.K29, U101.K30, U101.K31, U101.K32, U101.K33, U101.K34, U101.K35, U101.K36, U101.K37, U101.K38, U101.K39, U101.K40, U101.K41, U101.L11, U101.L12, U101.L13, U101.L14, U101.L15, U101.L16, U101.L17, U101.L18, U101.L19, U101.L20, U101.L21, U101.L22, U101.L23, U101.L24, U101.L25, U101.L26, U101.L27, U101.L28, U101.L29, U101.L30, U101.L31, U101.L32, U101.L33, U101.L34, U101.L35, U101.L36, U101.L37, U101.L38, U101.L39, U101.L40, U101.L41, U101.M11, U101.M12, U101.M13, U101.M14, U101.M15, U101.M16, U101.M17, U101.M18, U101.M19, U101.M20, U101.M21, U101.M22, U101.M23, U101.M24, U101.M25, U101.M26, U101.M27, U101.M28, U101.M29, U101.M30, U101.M31, U101.M32, U101.M33, U101.M34, U101.M35, U101.M36, U101.M37, U101.M38, U101.M39, U101.M40, U101.M41, U101.N11, U101.N12, U101.N13, U101.N14, U101.N15, U101.N16, U101.N17, U101.N18, U101.N19, U101.N20, U101.N21, U101.N22, U101.N23, U101.N24, U101.N25, U101.N26, U101.N27, U101.N28, U101.N29, U101.N30, U101.N31, U101.N32, U101.N33, U101.N34, U101.N35, U101.N36, U101.N37, U101.N38, U101.N39, U101.N40, U101.N41, U101.P11, U101.P12, U101.P13, U101.P14, U101.P15, U101.P16, U101.P17, U101.P18, U101.P19, U101.P20, U101.P21, U101.P22, U101.P23, U101.P24, U101.P25, U101.P26, U101.P27, U101.P28, U101.P29, U101.P30, U101.P31, U101.P32, U101.P33, U101.P34, U101.P35, U101.P36, U101.P37, U101.P38, U101.P39, U101.P40, U101.P41, U101.R11, U101.R12, U101.R13, U101.R14, U101.R15, U101.R16, U101.R17, U101.R18, U101.R19, U101.R20, U101.R21, U101.R22, U101.R23, U101.R24, U101.R25, U101.R26, U101.R27, U101.R28, U101.R29, U101.R30, U101.R31, U101.R32, U101.R33, U101.R34, U101.R35, U101.R36, U101.R37, U101.R38, U101.R39, U101.R40, U101.R41, U101.T11, U101.T12, U101.T13, U101.T14, U101.T15, U101.T16, U101.T17, U101.T18, U101.T19, U101.T20, U101.T21, U101.T22, U101.T23, U101.T24, U101.T25, U101.T26, U101.T27, U101.T28, U101.T29, U101.T30, U101.T31, U101.T32, U101.T33, U101.T34, U101.T35, U101.T36, U101.T37, U101.T38, U101.T39, U101.T40, U101.T41, U101.U11, U101.U12, U101.U13, U101.U14, U101.U15, U101.U16, U101.U17, U101.U18, U101.U19, U101.U20, U101.U21, U101.U22, U101.U23, U101.U24, U101.U25, U101.U26, U101.U27, U101.U28, U101.U29, U101.U30, U101.U31, U101.U32, U101.U33, U101.U34, U101.U35, U101.U36, U101.U37, U101.U38, U101.U39, U101.U40, U101.U41, U101.V11, U101.V12, U101.V13, U101.V14, U101.V15, U101.V16, U101.V17, U101.V18, U101.V19, U101.V20, U101.V21, U101.V22, U101.V23, U101.V24, U101.V25, U101.V26, U101.V27, U101.V28, U101.V29, U101.V30, U101.V31, U101.V32, U101.V33, U101.V34, U101.V35, U101.V36, U101.V37, U101.V38, U101.V39, U101.V40, U101.V41, U101.W11, U101.W12, U101.W13, U101.W14, U101.W15, U101.W16, U101.W17, U101.W18, U101.W19, U101.W20, U101.W21, U101.W22, U101.W23, U101.W24, U101.W25, U101.W26, U101.W27, U101.W28, U101.W29, U101.W30, U101.W31, U101.W32, U101.W33, U101.W34, U101.W35, U101.W36, U101.W37, U101.W38, U101.W39, U101.W40, U101.W41, U101.Y11, U101.Y12, U101.Y13, U101.Y14, U101.Y15, U101.Y16, U101.Y17, U101.Y18, U101.Y19, U101.Y20, U101.Y21, U101.Y22, U101.Y23, U101.Y24, U101.Y25, U101.Y26, U101.Y27, U101.Y28, U101.Y29, U101.Y30, U101.Y31, U101.Y32, U101.Y33, U101.Y34, U101.Y35, U101.Y36, U101.Y37, U101.Y38, U101.Y39, U101.Y40, U101.Y41, U201.AA11, U201.AA12, U201.AA13, U201.AA14, U201.AA15, U201.AA16, U201.AA17, U201.AA18, U201.AA19, U201.AA20, U201.AA21, U201.AA22, U201.AA23, U201.AA24, U201.AA25, U201.AA26, U201.AA27, U201.AA28, U201.AA29, U201.AA30, U201.AA31, U201.AA32, U201.AA33, U201.AA34, U201.AA35, U201.AA36, U201.AA37, U201.AA38, U201.AA39, U201.AA40, U201.AA41, U201.AB11, U201.AB12, U201.AB13, U201.AB14, U201.AB15, U201.AB16, U201.AB17, U201.AB18, U201.AB19, U201.AB20, U201.AB21, U201.AB22, U201.AB23, U201.AB24, U201.AB25, U201.AB26, U201.AB27, U201.AB28, U201.AB29, U201.AB30, U201.AB31, U201.AB32, U201.AB33, U201.AB34, U201.AB35, U201.AB36, U201.AB37, U201.AB38, U201.AB39, U201.AB40, U201.AB41, U201.AC11, U201.AC12, U201.AC13, U201.AC14, U201.AC15, U201.AC16, U201.AC17, U201.AC18, U201.AC19, U201.AC20, U201.AC21, U201.AC22, U201.AC23, U201.AC24, U201.AC25, U201.AC26, U201.AC27, U201.AC28, U201.AC29, U201.AC30, U201.AC31, U201.AC32, U201.AC33, U201.AC34, U201.AC35, U201.AC36, U201.AC37, U201.AC38, U201.AC39, U201.AC40, U201.AC41, U201.AD11, U201.AD12, U201.AD13, U201.AD14, U201.AD15, U201.AD16, U201.AD17, U201.AD18, U201.AD19, U201.AD20, U201.AD21, U201.AD22, U201.AD23, U201.AD24, U201.AD25, U201.AD26, U201.AD27, U201.AD28, U201.AD29, U201.AD30, U201.AD31, U201.AD32, U201.AD33, U201.AD34, U201.AD35, U201.AD36, U201.AD37, U201.AD38, U201.AD39, U201.AD40, U201.AD41, U201.AE11, U201.AE12, U201.AE13, U201.AE14, U201.AE15, U201.AE16, U201.AE17, U201.AE18, U201.AE19, U201.AE20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
SERDES_200G_A: U101.A7, U101.A8, U101.A9, U101.A10, U101.A11, U101.A12, U101.A13, U101.A14, U101.A15, U101.A16, U101.A17, U101.A18, U101.A19, U101.A20, U101.A21, U101.A22, U101.A23, U101.A24, U101.A25, U101.A26, U101.A27, U101.A28, U101.A29, U101.A30, U101.A31, U101.A32, U101.A33, U101.A34, U101.A35, U101.A36, U101.A37, U101.A38, U101.A39, U101.A40, U101.A41, U101.A42, U101.A43, U101.A44, U101.A45, U101.A46, U101.A47, U101.A48, U101.A49, U101.A50, U101.B7, U101.B8, U101.B9, U101.B10, U101.B11, U101.B12, U101.B13, U101.B14, U101.B15, U101.B16, U101.B17, U101.B18, U101.B19, U101.B20, U101.B21, U101.B22, U101.B23, U101.B24, U101.B25, U101.B26, U101.B27, U101.B28, U101.B29, U101.B30, U101.B31, U101.B32, U101.B33, U101.B34, U101.B35, U101.B36, U101.B37, U101.B38, U101.B39, U101.B40, U101.B41, U101.B42, U101.B43, U101.B44, U101.B45, U101.B46, U101.B47, U101.B48, U101.B49, U101.B50, U101.C7, U101.C8, U101.C9, U101.C10, U101.C11, U101.C12, U101.C13, U101.C14
SERDES_200G_B: U201.A7, U201.A8, U201.A9, U201.A10, U201.A11, U201.A12, U201.A13, U201.A14, U201.A15, U201.A16, U201.A17, U201.A18, U201.A19, U201.A20, U201.A21, U201.A22, U201.A23, U201.A24, U201.A25, U201.A26, U201.A27, U201.A28, U201.A29, U201.A30, U201.A31, U201.A32, U201.A33, U201.A34, U201.A35, U201.A36, U201.A37, U201.A38, U201.A39, U201.A40, U201.A41, U201.A42, U201.A43, U201.A44, U201.A45, U201.A46, U201.A47, U201.A48, U201.A49, U201.A50, U201.B7, U201.B8, U201.B9, U201.B10, U201.B11, U201.B12, U201.B13, U201.B14, U201.B15, U201.B16, U201.B17, U201.B18, U201.B19, U201.B20, U201.B21, U201.B22, U201.B23, U201.B24, U201.B25, U201.B26, U201.B27, U201.B28, U201.B29, U201.B30, U201.B31, U201.B32, U201.B33, U201.B34, U201.B35, U201.B36, U201.B37, U201.B38, U201.B39, U201.B40, U201.B41, U201.B42, U201.B43, U201.B44, U201.B45, U201.B46, U201.B47, U201.B48, U201.B49, U201.B50, U201.C7, U201.C8, U201.C9, U201.C10, U201.C11, U201.C12, U201.C13, U201.C14
TEC_TH_A: U102.25, U102.26
TEC_TH_B: U202.25, U202.26
TFLN_RF_A: U102.1, U102.2, U102.3, U102.4, U102.5, U102.6, U102.7, U102.8, U102.9, U102.10, U102.11, U102.12, U102.13, U102.14, U102.15, U102.16
TFLN_RF_B: U202.1, U202.2, U202.3, U202.4, U202.5, U202.6, U202.7, U202.8, U202.9, U202.10, U202.11, U202.12, U202.13, U202.14, U202.15, U202.16
THERMAL: U101.AE24, U101.AE25, U101.AE26, U101.AE27, U201.AE24, U201.AE25, U201.AE26, U201.AE27
VDD_IO: U101.C15, U101.C16, U101.C17, U101.C18, U101.C19, U101.C20, U101.C21, U101.C22, U101.C23, U101.C24, U101.C25, U101.C26, U101.C27, U101.C28, U101.C29, U101.C30, U101.C31, U101.C32, U101.C33, U101.C34, U101.C35, U101.C36, U101.C37, U101.C38, U101.C39, U101.C40, U101.C41, U101.C42, U101.C43, U101.C44, U101.D7, U101.D8, U101.D9, U101.D10, U101.D11, U101.D12, U101.D13, U101.D14, U101.D15, U101.D16, U101.D17, U101.D18, U101.D19, U101.D20, U101.D21, U101.D22, U101.D23, U101.D24, U101.D25, U101.D26, U101.D27, U101.D28, U101.D29, U101.D30, U101.D31, U101.D32, U101.D33, U101.D34, U101.D35, U101.D36, U101.D37, U101.D38, U101.D39, U101.D40, U101.D41, U101.D42, U101.D43, U101.D44, U101.E7, U101.E8, U101.E9, U101.E10, U101.E11, U101.E12, U101.E13, U101.E14, U101.E15, U101.E16, U101.E17, U101.E18, U101.E19, U101.E20, U101.E21, U101.E22, U101.E23, U101.E24, U101.E25, U101.E26, U101.E27, U101.E28, U101.E29, U101.E30, U101.E31, U101.E32, U101.E33, U101.E34, U201.C15, U201.C16, U201.C17, U201.C18, U201.C19, U201.C20, U201.C21, U201.C22, U201.C23, U201.C24, U201.C25, U201.C26, U201.C27, U201.C28, U201.C29, U201.C30, U201.C31, U201.C32, U201.C33, U201.C34, U201.C35, U201.C36, U201.C37, U201.C38, U201.C39, U201.C40, U201.C41, U201.C42, U201.C43, U201.C44, U201.D7, U201.D8, U201.D9, U201.D10, U201.D11, U201.D12, U201.D13, U201.D14, U201.D15, U201.D16, U201.D17, U201.D18, U201.D19, U201.D20, U201.D21, U201.D22, U201.D23, U201.D24, U201.D25, U201.D26, U201.D27, U201.D28, U201.D29, U201.D30, U201.D31, U201.D32, U201.D33, U201.D34, U201.D35, U201.D36, U201.D37, U201.D38, U201.D39, U201.D40, U201.D41, U201.D42, U201.D43, U201.D44, U201.E7, U201.E8, U201.E9, U201.E10, U201.E11, U201.E12, U201.E13, U201.E14, U201.E15, U201.E16, U201.E17, U201.E18, U201.E19, U201.E20, U201.E21, U201.E22, U201.E23, U201.E24, U201.E25, U201.E26, U201.E27, U201.E28, U201.E29, U201.E30, U201.E31, U201.E32, U201.E33, U201.E34
